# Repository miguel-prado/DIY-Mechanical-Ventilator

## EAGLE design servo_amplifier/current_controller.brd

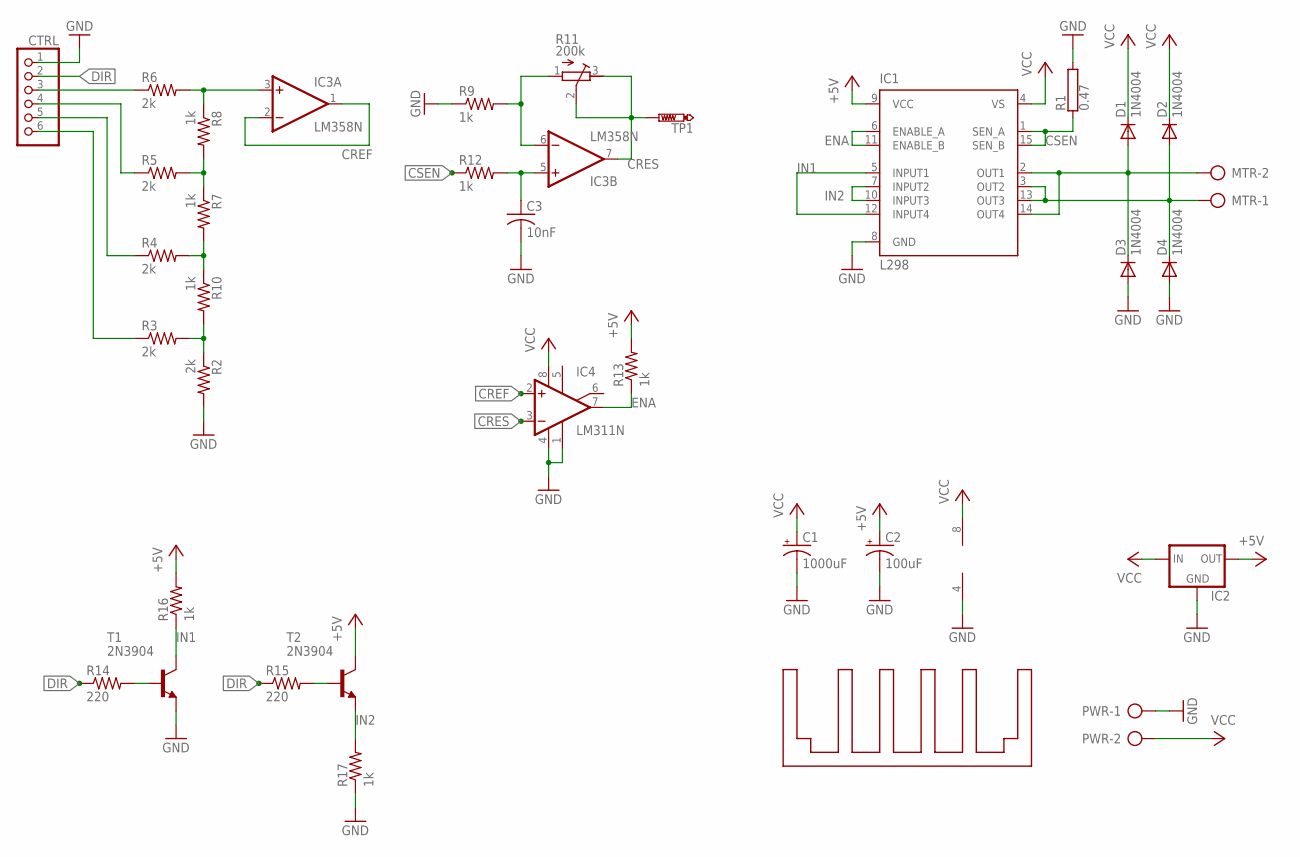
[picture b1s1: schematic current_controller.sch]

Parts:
C1: 1000uF; E5-13
C2: 100uF; E5-8,5
C3: 10nF; C050-024X044
CTRL: PINHD-1X6; 1X06
D1, D2, D3, D4: 1N4004; DO41-10
IC1: L298; MULTIWATT-15
IC2: 78XXS
IC3: LM358N; DIL08
IC4: LM311N; DIL08
MTR: AK500/2
PWR: AK500/2
R1: 0.47; CA4080
R2, R3, R4, R5, R6: 2k; 0204/7
R7, R8, R9, R10, R12, R13, R16, R17: 1k; 0204/7
R11: 200k; RTRIM64W
R14, R15: 220; 0204/7
T1, T2: 2N3904; TO92
TP1: PTR1PAD1-13Y; P1-13Y
U$1: MULTI15_HEATSINK

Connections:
+5V: C2.+, IC1.9 (VCC), IC2.OUT, R13.2, R16.2, T2.1 (C)
CREF: IC3.1 (OUT), IC3.2 (-IN), IC4.2 (+IN)
CRES: IC3.7 (OUT), IC4.3 (-IN), R11.2 (S), R11.3 (E), TP1.TP
CSEN: IC1.1 (SEN_A), IC1.15 (SEN_B), R1.1, R12.1
DIR: CTRL.2, R14.1, R15.1
ENA: IC1.6 (ENABLE_A), IC1.11 (ENABLE_B), IC4.7 (OUT), R13.1
GND: C1.-, C2.-, C3.2, CTRL.1, D3.A, D4.A, IC1.8 (GND), IC2.GND, IC3.4 (V-), IC4.1 (GND), IC4.4 (V-), PWR.1, R1.2, R2.2, R9.1, R17.1, T1.3 (E)
IN1: IC1.5 (INPUT1), IC1.12 (INPUT4), R16.1, T1.1 (C)
IN2: IC1.7 (INPUT2), IC1.10 (INPUT3), R17.2, T2.3 (E)
unnamed: D1.A, D3.C, IC1.2 (OUT1), IC1.14 (OUT4), MTR.2
unnamed: D2.A, D4.C, IC1.3 (OUT2), IC1.13 (OUT3), MTR.1
unnamed: R15.2, T2.2 (B)
unnamed: CTRL.3, R6.1
unnamed: CTRL.4, R5.1
unnamed: CTRL.5, R4.1
unnamed: CTRL.6, R3.1
unnamed: IC3.3 (+IN), R6.2, R8.1
unnamed: R5.2, R7.1, R8.2
unnamed: R4.2, R7.2, R10.1
unnamed: R2.1, R3.2, R10.2
unnamed: IC3.6 (-IN), R9.2, R11.1 (A)
unnamed: R14.2, T1.2 (B)
unnamed: C3.1, IC3.5 (+IN), R12.2
VCC: C1.+, D1.C, D2.C, IC1.4 (VS), IC2.IN, IC3.8 (V+), IC4.8 (V+), PWR.2

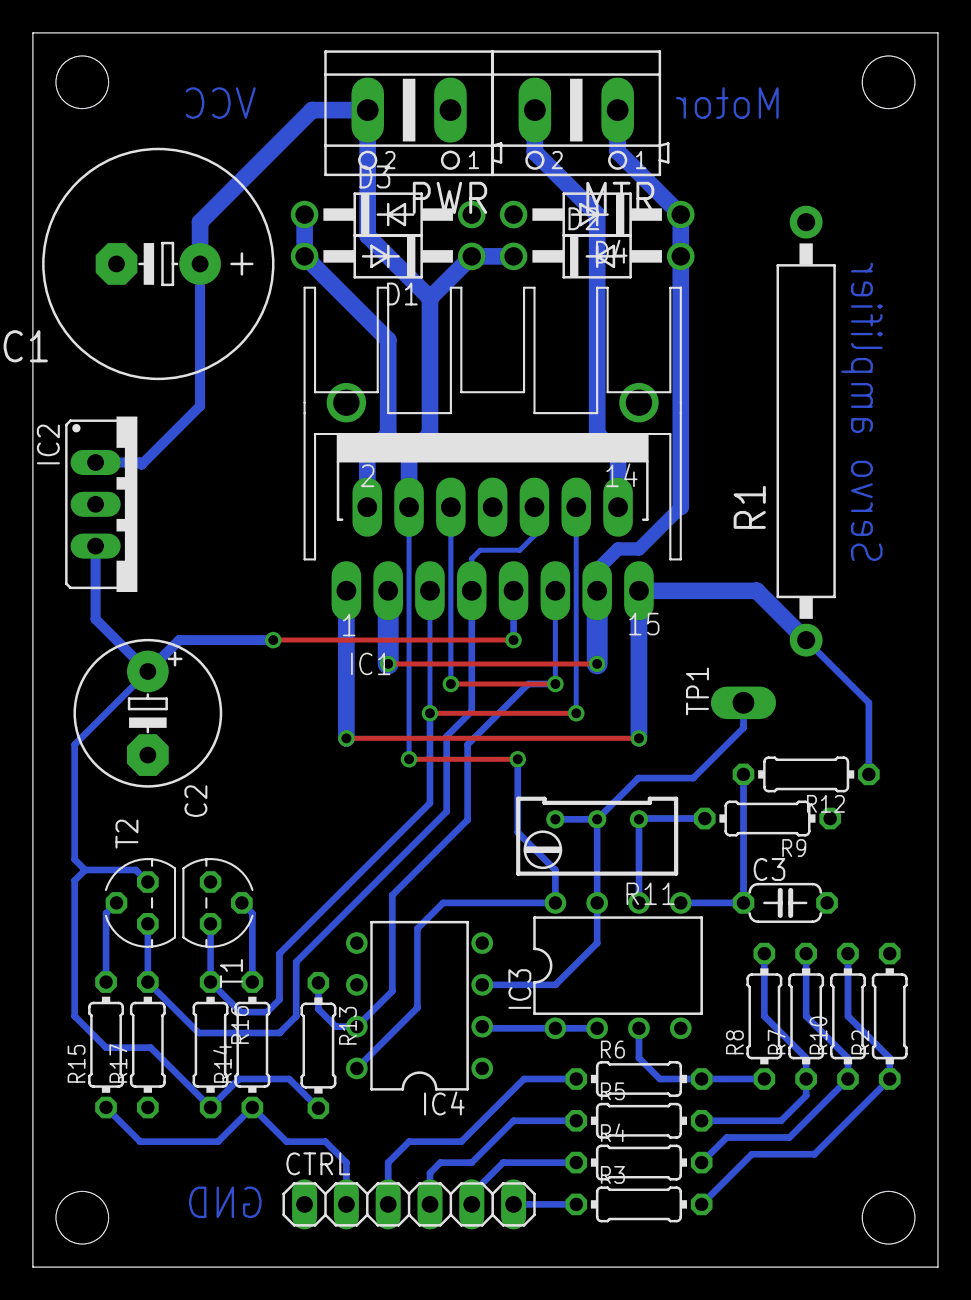
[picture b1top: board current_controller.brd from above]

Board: 2 copper layers, 55.0 x 75.0 mm, 35 parts (0 on the bottom side), 24 nets.

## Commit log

2020-04-09 Motion controller source
    Upload of main source and libraries for PID controller and velocity profile. In addition, here you can find the board files for the servo amplifier.
